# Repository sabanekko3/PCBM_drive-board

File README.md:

# PCBM_drive-board
[PCBステータ](https://github.com/sabanekko3/pcb_stator_v2)モーター用のドライバ基板  
kicad7で設計

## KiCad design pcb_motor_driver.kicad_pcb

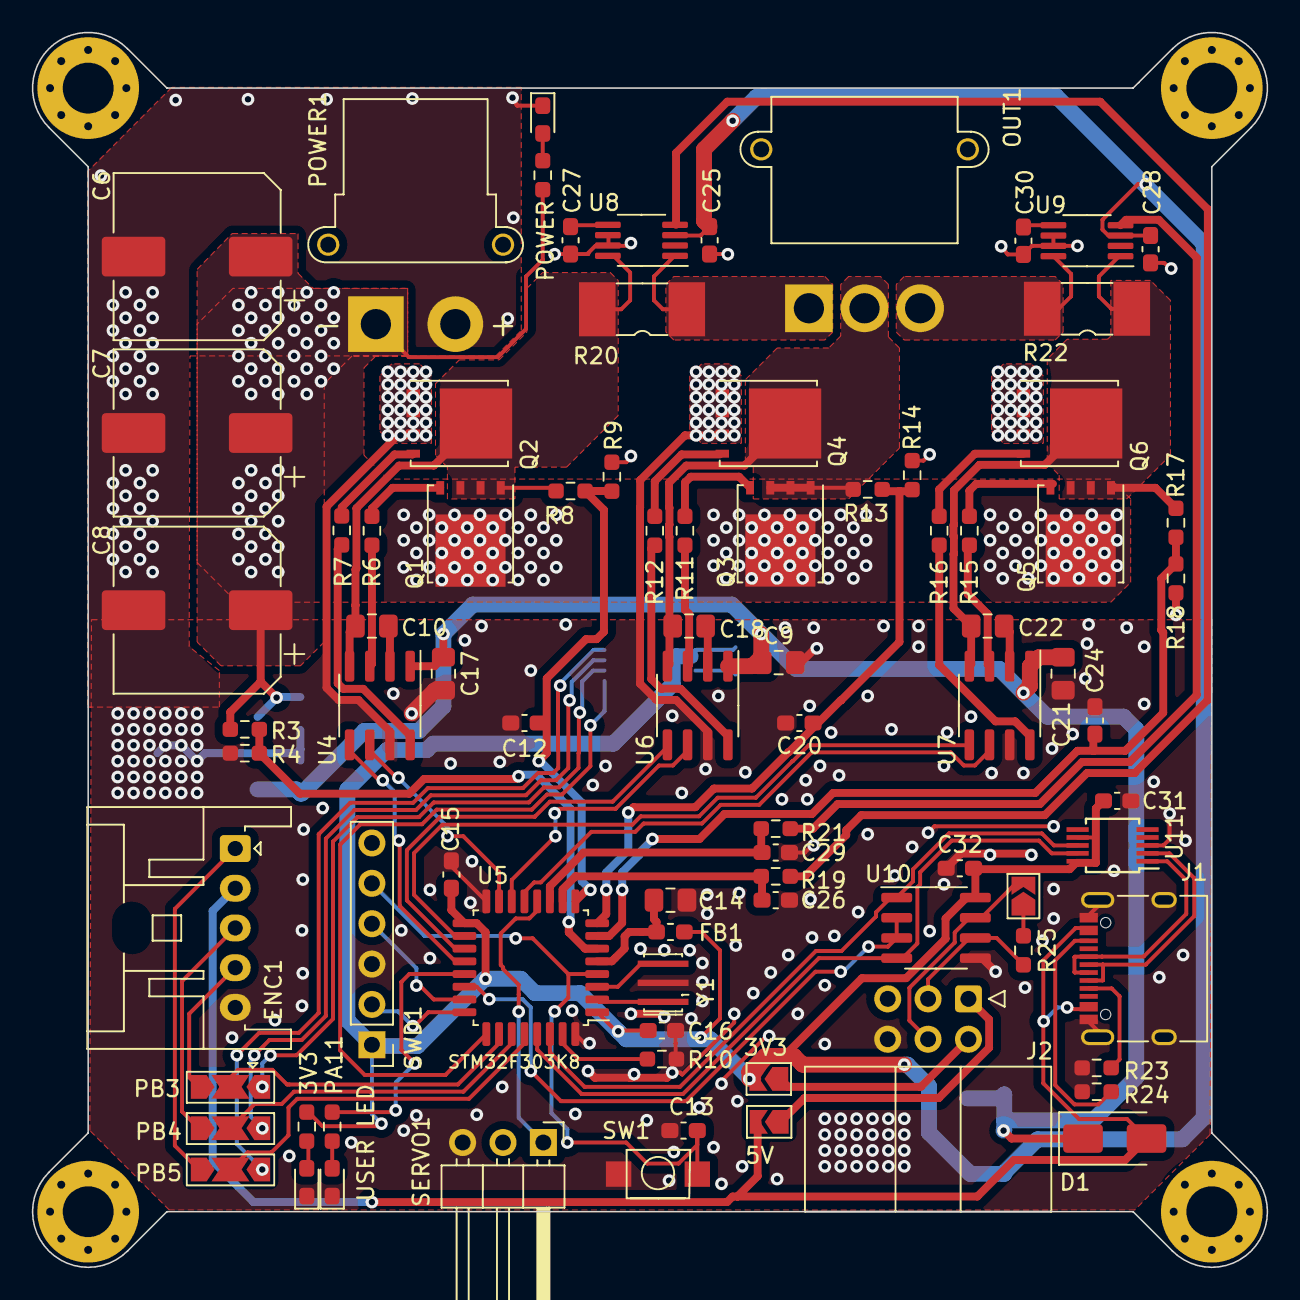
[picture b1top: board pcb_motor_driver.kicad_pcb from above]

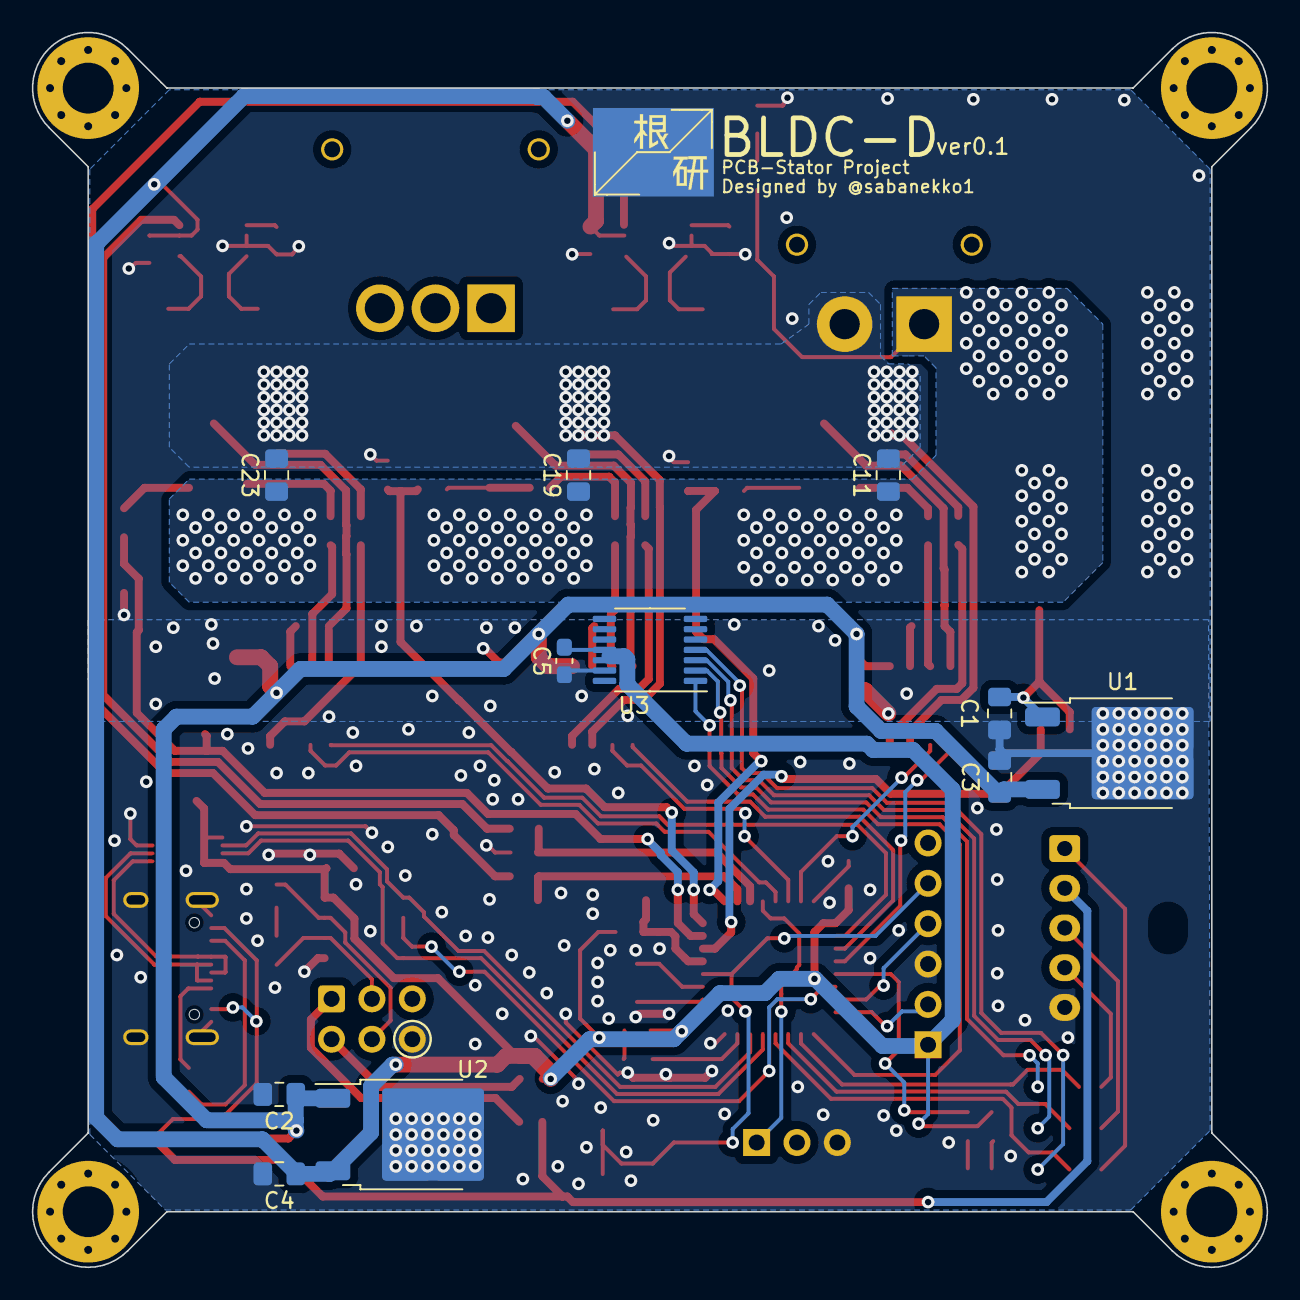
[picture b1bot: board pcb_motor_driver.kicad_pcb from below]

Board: 2 copper layers, 77.7 x 77.7 mm, 98 parts (11 on the bottom side), 75 nets.

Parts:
C1, C2, C3, C4, C9, C10, C11, C14, C17, C18, C19, C21, C22, C23: 4.7u; C_0805_2012Metric_Pad1.18x1.45mm_HandSolder
C5, C13, C15, C16, C25, C26, C27, C28, C29, C30, C31: 0.1u; C_0603_1608Metric_Pad1.08x0.95mm_HandSolder
C6, C7, C8: 330u; CP_Elec_10x10
C12, C20, C24: 1000p; C_0603_1608Metric_Pad1.08x0.95mm_HandSolder
C32: C; C_0603_1608Metric_Pad1.08x0.95mm_HandSolder
D1: D; D_SMA
D2, D3, D4: LED; LED_0603_1608Metric_Pad1.05x0.95mm_HandSolder
ENC1: Conn_01x05; JST_XA_S05B-XASK-1_1x05_P2.50mm_Horizontal
FB1: FerriteBead; L_0603_1608Metric_Pad1.05x0.95mm_HandSolder
H1, H2, H3, H4: MountingHole_Pad; MountingHole_3.2mm_M3_Pad_Via
J1: USB_C_Receptacle_USB2.0; USB_C_Receptacle_XKB_U262-16XN-4BVC11
J2: Conn_02x03_Odd_Even; IDC-Header_2x03_P2.54mm_Horizontal
JP1, JP2, JP3: Jumper_3_Open; SolderJumper-3_P2.0mm_Open_TrianglePad1.0x1.5mm
JP4, JP5, JP6: Jumper_2_Bridged; SolderJumper-2_P1.3mm_Open_TrianglePad1.0x1.5mm
OUT1: Conn_01x03; AMASS_MR30PW-M_1x03_P3.50mm_Horizontal
POWER1: Conn_01x02; AMASS_XT30PW-F_1x02_P2.50mm_Horizontal
Q1, Q2, Q3, Q4, Q5, Q6: BSC028N06LS3; TDSON-8-1
R1, R2, R3, R5, R8, R10, R13, R17, R19, R21: 10k; R_0603_1608Metric_Pad0.98x0.95mm_HandSolder
R4, R9, R14, R18: 1k; R_0603_1608Metric_Pad0.98x0.95mm_HandSolder
R6, R7, R11, R12, R15, R16: 10; R_0603_1608Metric_Pad0.98x0.95mm_HandSolder
R20, R22: 0.5m; PU2512
R23, R24: 5.1k; R_0603_1608Metric_Pad0.98x0.95mm_HandSolder
R25: 120; R_0603_1608Metric_Pad0.98x0.95mm_HandSolder
SERVO1: Conn_01x03; PinHeader_1x03_P2.54mm_Horizontal
SW1: SW_Push; TVAF06-A020B-R
SWD1: Conn_01x06; PinHeader_1x06_P2.54mm_Vertical
U1: 9V_LR; TO-252-2
U2: 3.3V_LR; TO-252-2
U3: AS5048A; TSSOP-14_4.4x5mm_P0.65mm
U4, U6, U7: MIC4604YM; SOIC-8_3.9x4.9mm_P1.27mm
U5: STM32F303K8Tx; LQFP-32_7x7mm_P0.8mm
U8, U9: MAX40056; MSOP-8_3x3mm_P0.65mm
U10: MAX3485; SOIC-8_3.9x4.9mm_P1.27mm
U11: CH340E; MSOP-10_3x3mm_P0.5mm
Y1: Resonator; Resonator_SMD_Murata_CSTxExxV-3Pin_3.0x1.1mm_HandSoldering

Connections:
+3.3V: C4.1, C5.2, C15.1, C16.1, C25.1, C28.1, C31.2, C32.2, FB1.1, JP6.2 (B), R1.1, SWD1.1, U2.3 (OUT), U3.11 (VDD5V), U3.12 (VDD3V), U5.1 (VDD), U5.17 (VDD), U8.3 (VDD), U9.3 (VDD), U10.8 (VCC), U11.7 (VCC), U11.10 (V3)
+5V: D1.2 (A), ENC1.2, J1.A4 (VBUS), J1.A9 (VBUS), J1.B4 (VBUS), J1.B9 (VBUS), JP5.2 (B)
+9V: C2.1, C3.1, C9.1, C17.1, C21.1, D1.1 (K), U1.3 (OUT), U2.1 (IN), U4.1 (VDD), U6.1 (VDD), U7.1 (VDD)
+BATT: C1.1, C6.1, C7.1, C8.1, C11.1, C19.1, C23.1, POWER1.1, Q1.5 (D), Q3.5 (D), Q5.5 (D), R3.1, R5.1, U1.1 (IN)
/BRIDGE1/OUT: C18.2, OUT1.2, Q3.1 (S), Q3.2 (S), Q3.3 (S), Q4.5 (D), R13.1, U6.4 (HS)
/BRIDGE1/PWM_H: U5.19 (PA9), U6.5 (HI)
/BRIDGE1/PWM_L: U5.14 (PB0), U6.6 (LI)
/BRIDGE1/SENS_V: C20.1, R13.2, R14.1, U5.8 (PA2)
/BRIDGE2/OUT: C22.2, Q5.1 (S), Q5.2 (S), Q5.3 (S), Q6.5 (D), R17.1, R22.1, U7.4 (HS), U9.1 (RS+)
/BRIDGE2/PWM_H: U5.18 (PA8), U7.5 (HI)
/BRIDGE2/PWM_L: U5.13 (PA7), U7.6 (LI)
/BRIDGE2/SENS_V: C24.1, R17.2, R18.1, U5.7 (PA1)
/BRIDGE/OUT: C10.2, Q1.1 (S), Q1.2 (S), Q1.3 (S), Q2.5 (D), R8.1, R20.2, U4.4 (HS), U8.8 (RS-)
/BRIDGE/PWM_H: U4.5 (HI), U5.20 (PA10)
/BRIDGE/PWM_L: U4.6 (LI), U5.15 (PB1)
/BRIDGE/SENS_V: C12.1, R8.2, R9.1, U5.9 (PA3)
/COMM/UART_DE: U5.22 (PA12), U10.2 (~RE), U10.3 (DE)
/COMM/UART_RX: U5.30 (PB7), U10.1 (RO), U11.8 (TXD)
/COMM/UART_TX: U5.29 (PB6), U10.4 (DI), U11.9 (RXD)
/I_SENS1/OUT: OUT1.3, R22.2, U9.8 (RS-)
/I_SENS1/SENS_I: C29.1, R21.1, U5.11 (PA5)
/I_SENS/IN: OUT1.1, R20.1, U8.1 (RS+)
/I_SENS/SENS_I: C26.1, R19.1, U5.10 (PA4)
/MCU/LED1: R2.1, U5.21 (PA11)
/MCU/POWER_V: R3.2, R4.1, U5.6 (PA0)
/MCU/SERVO_PWM: SERVO1.1, U5.12 (PA6)
/MCU/SPI_MISO: JP2.2 (C), U5.27 (PB4)
/MCU/SPI_MOSI: JP1.2 (C), U5.28 (PB5)
/MCU/SPI_SCK: JP3.2 (C), U5.26 (PB3)
/MCU/SS: U3.1 (~CSn), U5.25 (PA15)
GND: C1.2, C2.2, C3.2, C4.2, C5.1, C6.2, C7.2, C8.2, C9.2, C11.2, C12.2, C13.2, C14.2, C15.2, C16.2, C17.2, C19.2, C20.2, C21.2, C23.2, C24.2, C25.2, C26.2, C27.2, C28.2, C29.2, C30.2, C31.1, C32.1, D2.1 (K), D3.1 (K), D4.1 (K), ENC1.5, J1.A1 (GND), J1.A12 (GND), J1.B1 (GND), J1.B12 (GND), J1.S1 (SHIELD), J2.6, POWER1.2, Q2.1 (S), Q2.2 (S), Q2.3 (S), Q4.1 (S), Q4.2 (S), Q4.3 (S), Q6.1 (S), Q6.2 (S), Q6.3 (S), R4.2, R9.2, R10.2, R14.2, R18.2, R23.2, R24.2, SERVO1.3, SW1.1, SWD1.3, U1.2 (GND), U2.2 (GND), U3.13 (GND), U4.7 (VSS), U5.16 (VSS), U5.32 (VSS), U6.7 (VSS), U7.7 (VSS), U8.6 (GND), U8.7 (CIP), U9.6 (GND), U9.7 (CIP), U10.5 (GND), U11.3 (GND), Y1.2
NRST: C13.1, SW1.2, SWD1.5, U5.4 (NRST)
unnamed: D2.2 (A), R1.2
unnamed: D3.2 (A), R2.2
unnamed: D4.2 (A), R5.2
unnamed: ENC1.1, JP1.3 (B)
unnamed: ENC1.3, JP2.3 (B)
unnamed: ENC1.4, JP3.3 (B)
unnamed: J1.A5 (CC1), R23.1
unnamed: J1.B5 (CC2), R24.1
unnamed: J2.1, JP5.1 (A)
unnamed: J2.2, JP6.1 (A)
unnamed: J2.3, R25.1, U10.6 (A)
unnamed: J2.4, JP4.2 (B), U10.7 (B)
unnamed: JP1.1 (A), U3.4 (MOSI)
unnamed: JP2.1 (A), U3.3 (MISO)
unnamed: JP3.1 (A), U3.2 (CLK)
unnamed: JP4.1 (A), R25.2
unnamed: Q1.4 (G), R6.2
unnamed: Q2.4 (G), R7.2
unnamed: Q3.4 (G), R11.2
unnamed: Q4.4 (G), R12.2
unnamed: Q5.4 (G), R15.2
unnamed: Q6.4 (G), R16.2
unnamed: C10.1, U4.2 (HB)
unnamed: R6.1, U4.3 (HO)
unnamed: R7.1, U4.8 (LO)
unnamed: R10.1, U5.31 (BOOT0)
unnamed: U5.2 (PF0), Y1.1
unnamed: U5.3 (PF1), Y1.3
unnamed: C14.1, FB1.2, U5.5 (VDDA)
unnamed: C18.1, U6.2 (HB)
unnamed: R11.1, U6.3 (HO)
unnamed: R12.1, U6.8 (LO)
unnamed: C22.1, U7.2 (HB)
unnamed: R15.1, U7.3 (HO)
unnamed: R16.1, U7.8 (LO)
unnamed: R19.2, U8.4 (OUT)
unnamed: C27.1, U8.5 (REF)
unnamed: R21.2, U9.4 (OUT)
unnamed: C30.1, U9.5 (REF)
unnamed: J1.A6 (D+), J1.B6 (D+), U11.1 (UD+)
unnamed: J1.A7 (D-), J1.B7 (D-), U11.2 (UD-)
SWCLK: SWD1.2, U5.24 (PA14)
SWDIO: SWD1.4, U5.23 (PA13)

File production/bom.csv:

Designator,Footprint,Quantity,Value,LCSC Part #
C1,0805,1,4.7u,
C10,0805,1,4.7u,
C11,0805,1,4.7u,
C12,0603,1,1000p,
C13,0603,1,0.1u,
C14,0805,1,4.7u,
C15,0603,1,0.1u,
C16,0603,1,0.1u,
C17,0805,1,4.7u,
C18,0805,1,4.7u,
C19,0805,1,4.7u,
C2,0805,1,4.7u,
C20,0603,1,1000p,
C21,0805,1,4.7u,
C22,0805,1,4.7u,
C23,0805,1,4.7u,
C24,0603,1,1000p,
C25,0603,1,0.1u,
C26,0603,1,0.1u,
C27,0603,1,0.1u,
C28,0603,1,0.1u,
C29,0603,1,0.1u,
C3,0805,1,4.7u,
C30,0603,1,0.1u,
C31,0603,1,0.1u,
C32,0603,1,C,
C4,0805,1,4.7u,
C5,0603,1,0.1u,
"C6, C7, C8",CP_Elec_10x10,3,330u,
C9,0805,1,4.7u,
D1,D_SMA,1,D,
D2,0603,1,LED,
D3,0603,1,LED,
D4,0603,1,LED,
ENC1,JST_XA_S05B-XASK-1_1x05_P2.50mm_Horizontal,1,Conn_01x05,
FB1,0603,1,FerriteBead,
"H1, H2, H3, H4",MountingHole_3.2mm_M3_Pad_Via,4,MountingHole_Pad,
J1,USB_C_Receptacle_XKB_U262-16XN-4BVC11,1,USB_C_Receptacle_USB2.0,
J2,IDC-Header_2x03_P2.54mm_Horizontal,1,Conn_02x03_Odd_Even,
"JP1, JP2, JP3",SolderJumper-3_P2.0mm_Open_TrianglePad1.0x1.5mm,3,Jumper_3_Open,
"JP4, JP5, JP6",SolderJumper-2_P1.3mm_Open_TrianglePad1.0x1.5mm,3,Jumper_2_Bridged,
OUT1,AMASS_MR30PW-M_1x03_P3.50mm_Horizontal,1,Conn_01x03,
POWER1,AMASS_XT30PW-F_1x02_P2.50mm_Horizontal,1,Conn_01x02,
"Q1, Q2, Q3, Q4, Q5, Q6",TDSON-8-1,6,BSC028N06LS3,
R1,0603,1,10k,
R10,0603,1,10k,
R11,0603,1,10,
R12,0603,1,10,
R13,0603,1,10k,
R14,0603,1,1k,
R15,0603,1,10,
R16,0603,1,10,
R17,0603,1,10k,
R18,0603,1,1k,
R19,0603,1,10k,
R2,0603,1,10k,
"R20, R22",PU2512,2,0.5m,
R21,0603,1,10k,
R23,0603,1,5.1k,
R24,0603,1,5.1k,
R25,0603,1,120,
R3,0603,1,10k,
R4,0603,1,1k,
R5,0603,1,10k,
R6,0603,1,10,
R7,0603,1,10,
R8,0603,1,10k,
R9,0603,1,1k,
SERVO1,PinHeader_1x03_P2.54mm_Horizontal,1,Conn_01x03,
SW1,TVAF06-A020B-R,1,SW_Push,
SWD1,PinHeader_1x06_P2.54mm_Vertical,1,Conn_01x06,
U1,TO-252-2,1,9V_LR,
U10,SOIC-8_3.9x4.9mm_P1.27mm,1,MAX3485,
U11,MSOP-10_3x3mm_P0.5mm,1,CH340E,
U2,TO-252-2,1,3.3V_LR,
U3,TSSOP-14_4.4x5mm_P0.65mm,1,AS5048A,
"U4, U6, U7",SOIC-8_3.9x4.9mm_P1.27mm,3,MIC4604YM,
U5,LQFP-32_7x7mm_P0.8mm,1,STM32F303K8Tx,
"U8, U9",MSOP-8_3x3mm_P0.65mm,2,MAX40056,
Y1,Resonator_SMD_Murata_CSTxExxV-3Pin_3.0x1.1mm_HandSoldering,1,Resonator,

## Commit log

2023-05-05 first
